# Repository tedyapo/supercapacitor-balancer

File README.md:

# supercapacitor-balancer
Charge balance PCB for 12V nominal (16.2V max) supercapacitor bank

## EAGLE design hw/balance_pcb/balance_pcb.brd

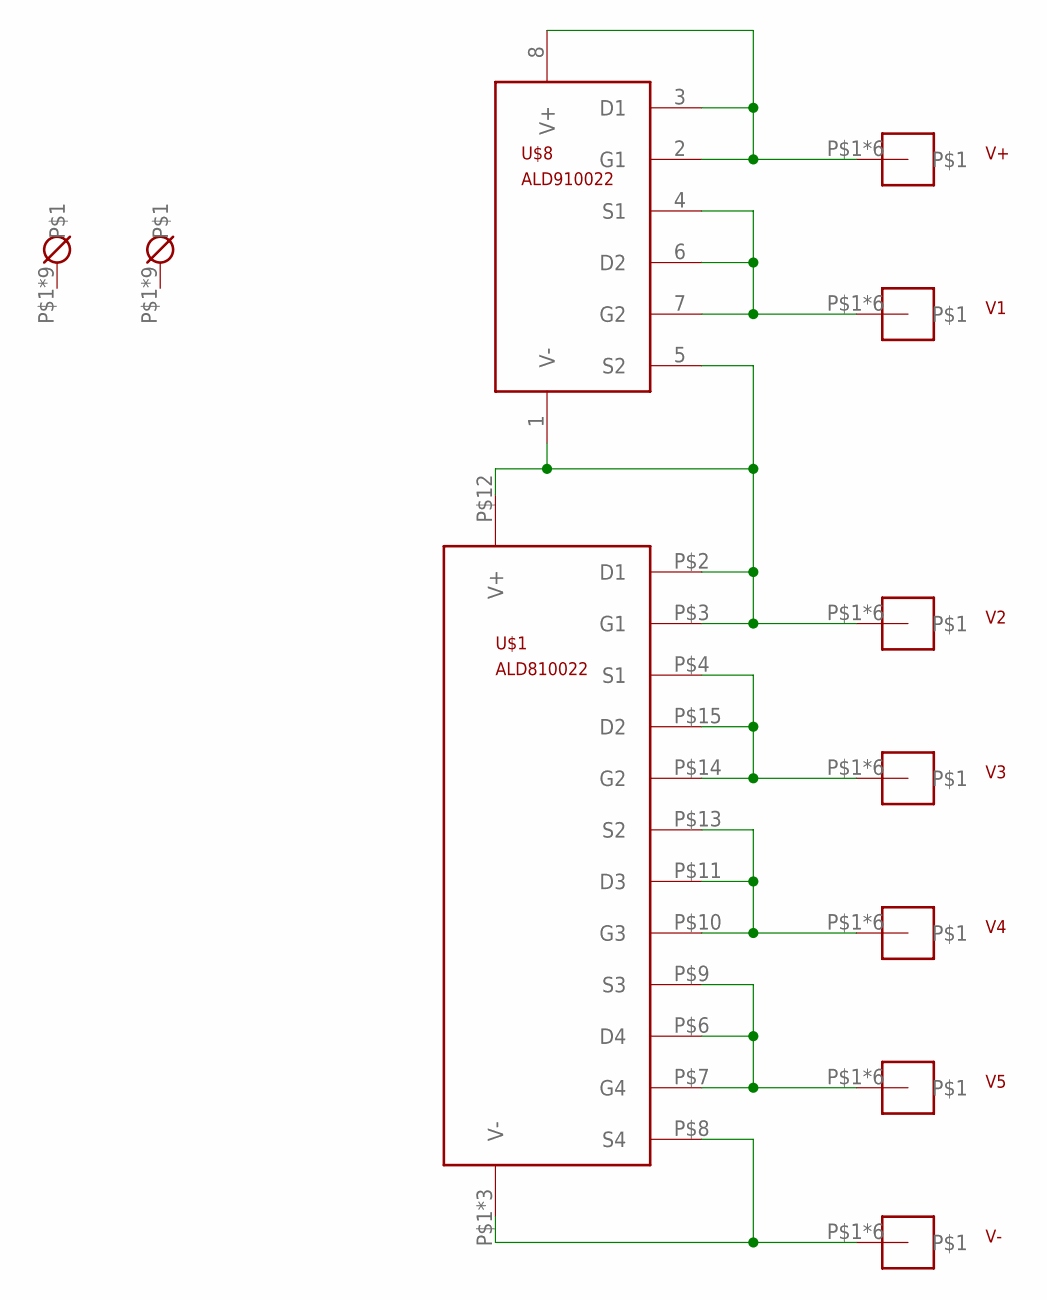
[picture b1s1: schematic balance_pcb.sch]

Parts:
U$1: ALD810022; SOIC16_NARROW
U$2, U$3: MOUNTING_HOLE; MOUNTING_HOLE_#4
U$8: ALD910022; SOIC8
V1, V2, V3, V4, V5: WIRE_PAD100MIL; WIRE_PAD
V+: WIRE_PAD100MIL; WIRE_PAD
V-: WIRE_PAD100MIL; WIRE_PAD

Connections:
unnamed: U$1.P$1 (V-), U$1.P$5 (V-), U$1.P$8 (S4), U$1.P$16 (V-), V-.P$1, V-.P$2, V-.P$3, V-.P$4, V-.P$5, V-.P$6
unnamed: U$1.P$10 (G3), U$1.P$11 (D3), U$1.P$13 (S2), V4.P$1, V4.P$2, V4.P$3, V4.P$4, V4.P$5, V4.P$6
unnamed: U$8.4 (S1), U$8.6 (D2), U$8.7 (G2), V1.P$1, V1.P$2, V1.P$3, V1.P$4, V1.P$5, V1.P$6
unnamed: U$1.P$6 (D4), U$1.P$7 (G4), U$1.P$9 (S3), V5.P$1, V5.P$2, V5.P$3, V5.P$4, V5.P$5, V5.P$6
unnamed: U$1.P$4 (S1), U$1.P$14 (G2), U$1.P$15 (D2), V3.P$1, V3.P$2, V3.P$3, V3.P$4, V3.P$5, V3.P$6
unnamed: U$8.2 (G1), U$8.3 (D1), U$8.8 (V+), V+.P$1, V+.P$2, V+.P$3, V+.P$4, V+.P$5, V+.P$6
unnamed: U$1.P$2 (D1), U$1.P$3 (G1), U$1.P$12 (V+), U$8.1 (V-), U$8.5 (S2), V2.P$1, V2.P$2, V2.P$3, V2.P$4, V2.P$5, V2.P$6

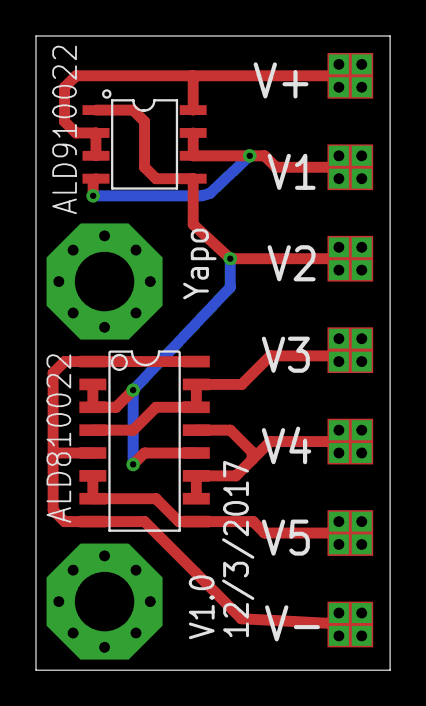
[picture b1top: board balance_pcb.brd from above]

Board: 2 copper layers, 19.7 x 35.2 mm, 11 parts (0 on the bottom side), 7 nets.

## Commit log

2017-12-03 added first rev of charge balance PCB
